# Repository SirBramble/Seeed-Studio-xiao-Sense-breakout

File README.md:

# Seeed Studio xiao Sense breakout

Small breakout Board for the [Seed Studio Xiao ESP32S3 Sense with camera](https://www.mouser.de/ProductDetail/713-113991115)
## Pictures

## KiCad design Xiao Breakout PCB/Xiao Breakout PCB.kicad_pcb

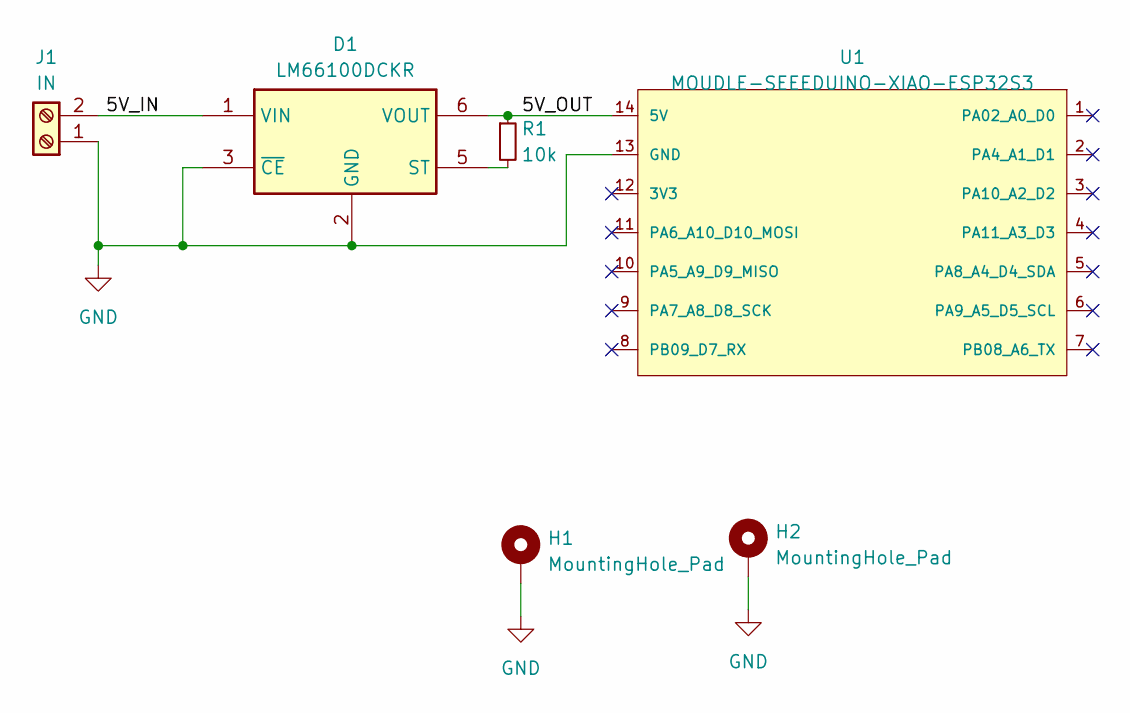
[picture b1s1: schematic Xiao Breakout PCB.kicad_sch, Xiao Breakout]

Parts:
D1: LM66100DCKR; SOP65P210X110-6N; Mouser Part Number 595-LM66100DCKR
H1, H2: MountingHole_Pad; MountingHole_3.2mm_M3_DIN965_Pad
J1: IN; TerminalBlock_bornier-2_P5.08mm
R1: 10k; R_0603_1608Metric
U1: MOUDLE-SEEEDUINO-XIAO-ESP32S3; MOUDLE14P-SMD-2.54-21X17.8MM

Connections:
/5V_IN: D1.1 (VIN), J1.2
/5V_OUT: D1.6 (VOUT), R1.1, U1.14 (5V)
GND: D1.2 (GND), D1.3 (~CE), H1.1, H2.1, J1.1, U1.13 (GND)
unnamed: D1.5 (ST), R1.2

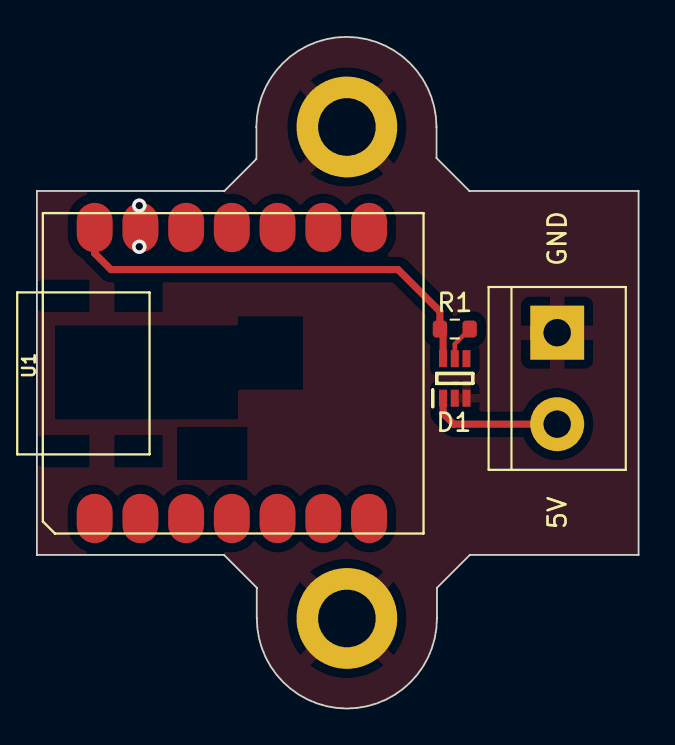
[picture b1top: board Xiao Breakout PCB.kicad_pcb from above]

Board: 2 copper layers, 33.4 x 37.3 mm, 6 parts (0 on the bottom side), 4 nets.

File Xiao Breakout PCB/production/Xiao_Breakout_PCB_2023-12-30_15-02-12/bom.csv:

Designator,Footprint,Quantity,Value,LCSC Part #
D1,SOP65P210X110-6N,1,LM66100DCKR,
"H1, H2",MountingHole_3.2mm_M3_DIN965_Pad,2,MountingHole_Pad,
J1,TerminalBlock_bornier-2_P5.08mm,1,IN,
R1,0603,1,10k,
U1,MOUDLE14P-SMD-2.54-21X17.8MM,1,MOUDLE-SEEEDUINO-XIAO-ESP32S3,

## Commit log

2023-12-30 added pictures
2023-12-30 added TN
2024-01-21 added 3D
